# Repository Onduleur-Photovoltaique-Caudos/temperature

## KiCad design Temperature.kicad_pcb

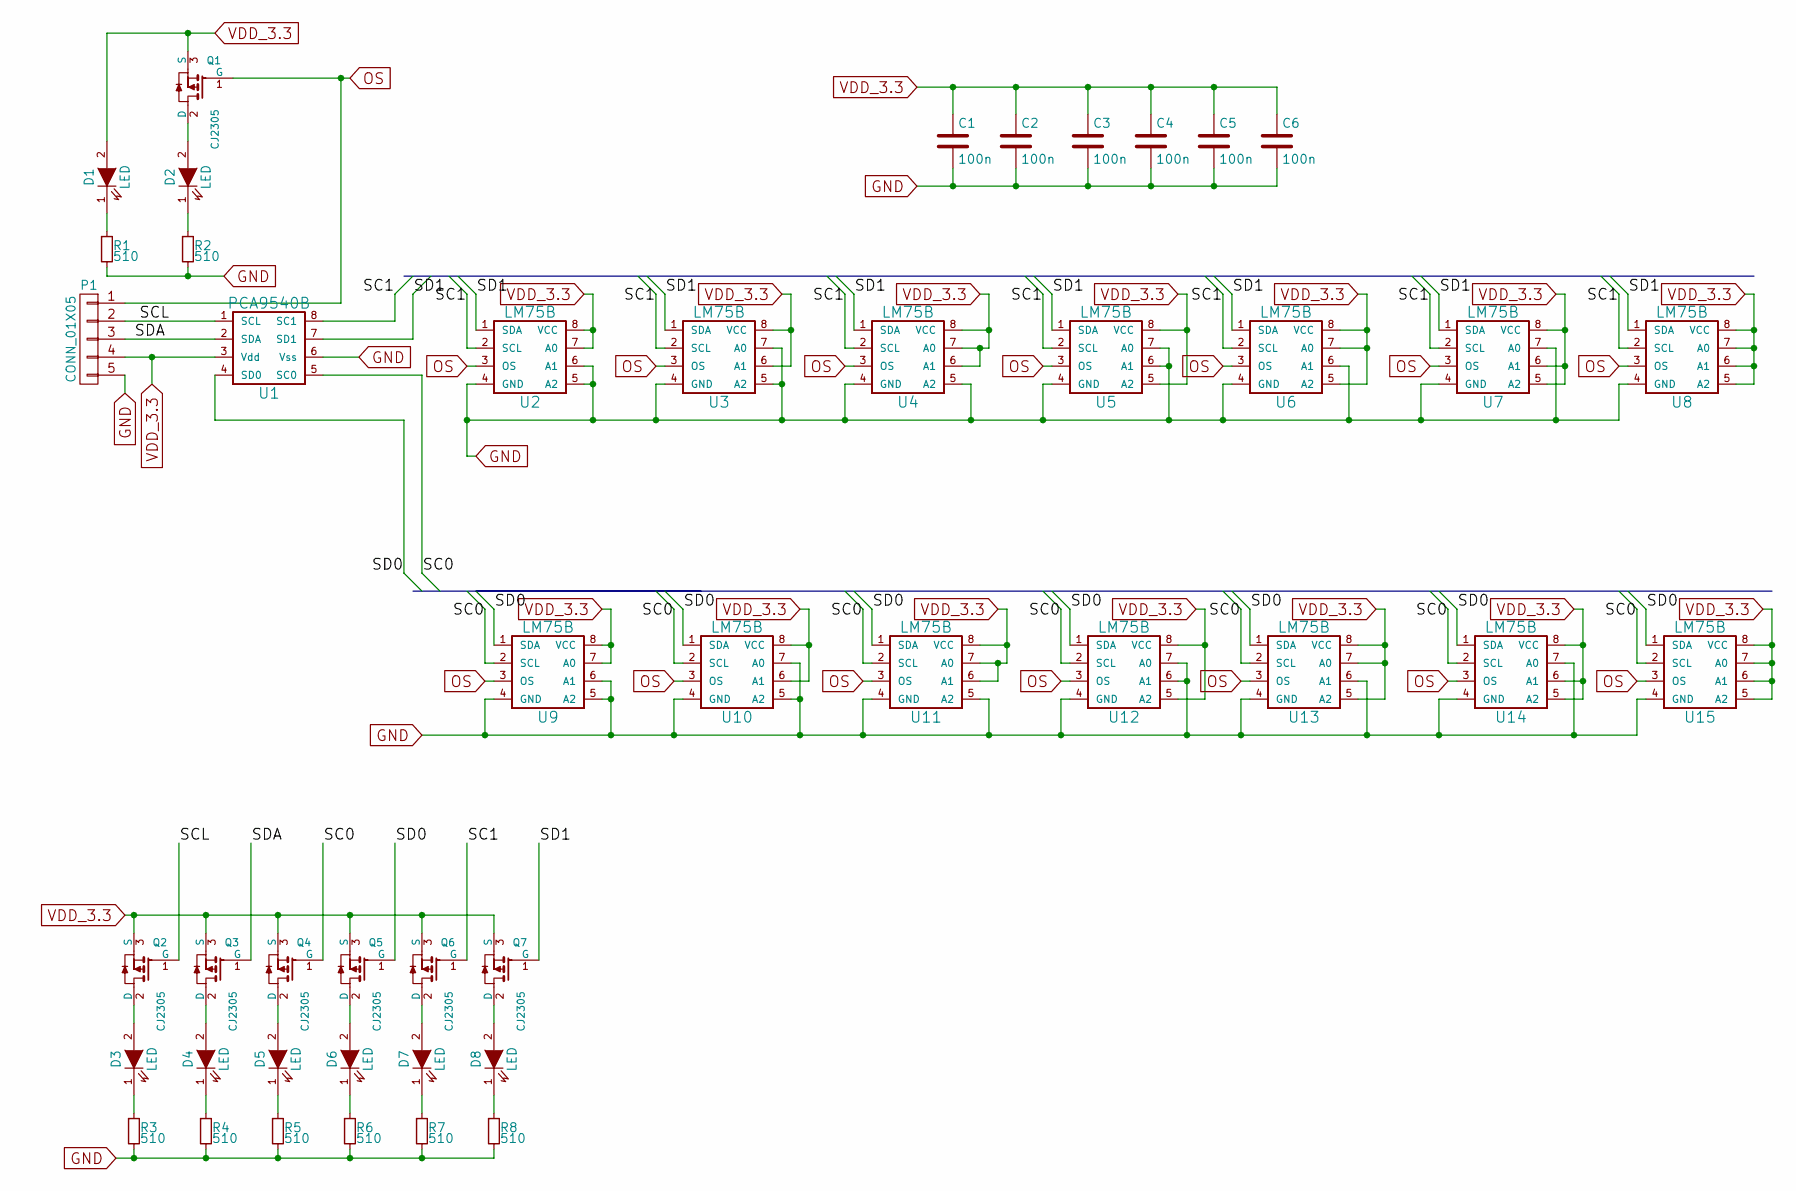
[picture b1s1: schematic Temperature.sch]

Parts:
C1, C2, C3, C4, C5, C6: 100n; C_0603; Manufacturer PN C1608X7R1H104K080AA; Mouser SKU 810-C1608X7R1H104K
D1, D2, D3, D4, D5, D6, D7, D8: LED; LED-0603
P1: CONN_01X05; pin_1x5_metric
Q1, Q2, Q3, Q4, Q5, Q6, Q7: CJ2305; SOT-23; Manufacturer PN CJ2305; Mouser SKU None
R1: 510; R_0603
R2, R3, R4, R5, R6, R7, R8: 510; R_0603_HandSoldering
U1: PCA9540B; SOIC-8-N
U2, U3, U4, U5, U6, U7, U8, U9, U10, U11, U12, U13, U14, U15: LM75B; SOIC-8-N

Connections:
/SC0: Q4.1 (G), U1.5 (SC0), U9.2 (SCL), U10.2 (SCL), U11.2 (SCL), U12.2 (SCL), U13.2 (SCL), U14.2 (SCL), U15.2 (SCL)
/SC1: Q6.1 (G), U1.8 (SC1), U2.2 (SCL), U3.2 (SCL), U4.2 (SCL), U5.2 (SCL), U6.2 (SCL), U7.2 (SCL), U8.2 (SCL)
/SCL: P1.2, Q2.1 (G), U1.1 (SCL)
/SD0: Q5.1 (G), U1.4 (SD0), U9.1 (SDA), U10.1 (SDA), U11.1 (SDA), U12.1 (SDA), U13.1 (SDA), U14.1 (SDA), U15.1 (SDA)
/SD1: Q7.1 (G), U1.7 (SD1), U2.1 (SDA), U3.1 (SDA), U4.1 (SDA), U5.1 (SDA), U6.1 (SDA), U7.1 (SDA), U8.1 (SDA)
/SDA: P1.3, Q3.1 (G), U1.2 (SDA)
GND: C1.2, C2.2, C3.2, C4.2, C5.2, C6.2, P1.5, R1.2, R2.2, R3.2, R4.2, R5.2, R6.2, R7.2, R8.2, U1.6 (Vss), U2.4 (GND), U2.5 (A2), U2.6 (A1), U3.4 (GND), U3.5 (A2), U3.7 (A0), U4.4 (GND), U4.5 (A2), U5.4 (GND), U5.6 (A1), U5.7 (A0), U6.4 (GND), U6.6 (A1), U7.4 (GND), U7.7 (A0), U8.4 (GND), U9.4 (GND), U9.5 (A2), U9.6 (A1), U10.4 (GND), U10.5 (A2), U10.7 (A0), U11.4 (GND), U11.5 (A2), U12.4 (GND), U12.6 (A1), U12.7 (A0), U13.4 (GND), U13.6 (A1), U14.4 (GND), U14.7 (A0), U15.4 (GND)
unnamed: D1.1 (K), R1.1
unnamed: D2.1 (K), R2.1
unnamed: D2.2 (A), Q1.2 (D)
unnamed: D3.1 (K), R3.1
unnamed: D3.2 (A), Q2.2 (D)
unnamed: D4.1 (K), R4.1
unnamed: D4.2 (A), Q3.2 (D)
unnamed: D5.1 (K), R5.1
unnamed: D5.2 (A), Q4.2 (D)
unnamed: D6.1 (K), R6.1
unnamed: D6.2 (A), Q5.2 (D)
unnamed: D7.1 (K), R7.1
unnamed: D7.2 (A), Q6.2 (D)
unnamed: D8.1 (K), R8.1
unnamed: D8.2 (A), Q7.2 (D)
OS: P1.1, Q1.1 (G), U2.3 (OS), U3.3 (OS), U4.3 (OS), U5.3 (OS), U6.3 (OS), U7.3 (OS), U8.3 (OS), U9.3 (OS), U10.3 (OS), U11.3 (OS), U12.3 (OS), U13.3 (OS), U14.3 (OS), U15.3 (OS)
VDD_3.3: C1.1, C2.1, C3.1, C4.1, C5.1, C6.1, D1.2 (A), P1.4, Q1.3 (S), Q2.3 (S), Q3.3 (S), Q4.3 (S), Q5.3 (S), Q6.3 (S), Q7.3 (S), U1.3 (Vdd), U2.7 (A0), U2.8 (VCC), U3.6 (A1), U3.8 (VCC), U4.6 (A1), U4.7 (A0), U4.8 (VCC), U5.5 (A2), U5.8 (VCC), U6.5 (A2), U6.7 (A0), U6.8 (VCC), U7.5 (A2), U7.6 (A1), U7.8 (VCC), U8.5 (A2), U8.6 (A1), U8.7 (A0), U8.8 (VCC), U9.7 (A0), U9.8 (VCC), U10.6 (A1), U10.8 (VCC), U11.6 (A1), U11.7 (A0), U11.8 (VCC), U12.5 (A2), U12.8 (VCC), U13.5 (A2), U13.7 (A0), U13.8 (VCC), U14.5 (A2), U14.6 (A1), U14.8 (VCC), U15.5 (A2), U15.6 (A1), U15.7 (A0), U15.8 (VCC)

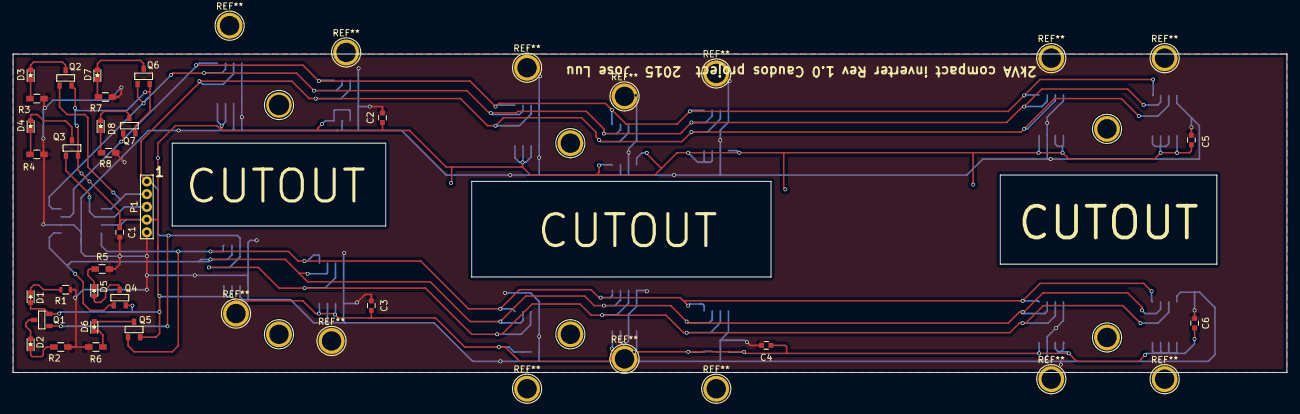
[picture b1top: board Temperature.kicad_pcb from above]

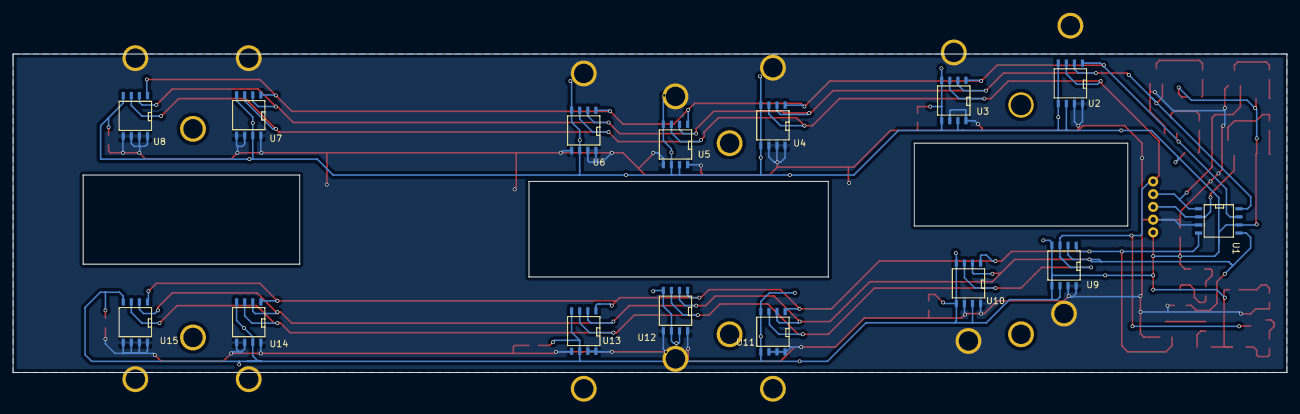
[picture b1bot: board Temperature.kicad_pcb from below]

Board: 2 copper layers, 200.0 x 50.0 mm, 45 parts (15 on the bottom side), 24 nets.

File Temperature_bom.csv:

"Id";"Designator";"Package";"Quantity";"Designation";"Supplier and ref";
1;"U1";"SOIC-8-N";1;"PCA9540B";;;
2;"U2,U3,U4,U5,U6,U7,U8,U9,U10,U11,U12,U13,U14,U15";"SOIC-8-N";14;"LM75B";;;
3;"C1,C2,C3,C4,C5,C6";"C_0603";6;"100n";;;
4;"P1";"pin_1x5_metric";1;"CONN_01X05";;;
5;"D1,D2,D3,D4,D5,D6,D7,D8";"LED-0603";8;"LED";;;
6;"R1";"R_0603";1;"510";;;
7;"R2,R3,R4,R5,R6,R7,R8";"R_0603_HandSoldering";7;"510";;;
8;"Q1,Q2,Q3,Q4,Q5,Q6,Q7";"SOT-23";7;"CJ2305";;;
9;"REF**,REF**,REF**,REF**,REF**,REF**";"1pin";6;"1pin";;;

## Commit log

2020-04-22 forgot 2 files
